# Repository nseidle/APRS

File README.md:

APRS Entry for 2016 SparkFun AVC
===========================================================

This repo contains all the code and PCB layouts used on the A+PRS vehicle Alicia and I entered in the 2016 SparkFun AVC.

Repository Contents
-------------------

The vehicle is broken into sub-systems in order to eat the elephant. Each directory is a sub-system.

Documentation
--------------

There's a tutorial being written.

License Information
-------------------

This is _**open source**_! 

Please use, reuse, and modify these files as you see fit. Please maintain attribution to SparkFun Electronics. Any derivative must be released under the same license.

Distributed as-is; no warranty is given.

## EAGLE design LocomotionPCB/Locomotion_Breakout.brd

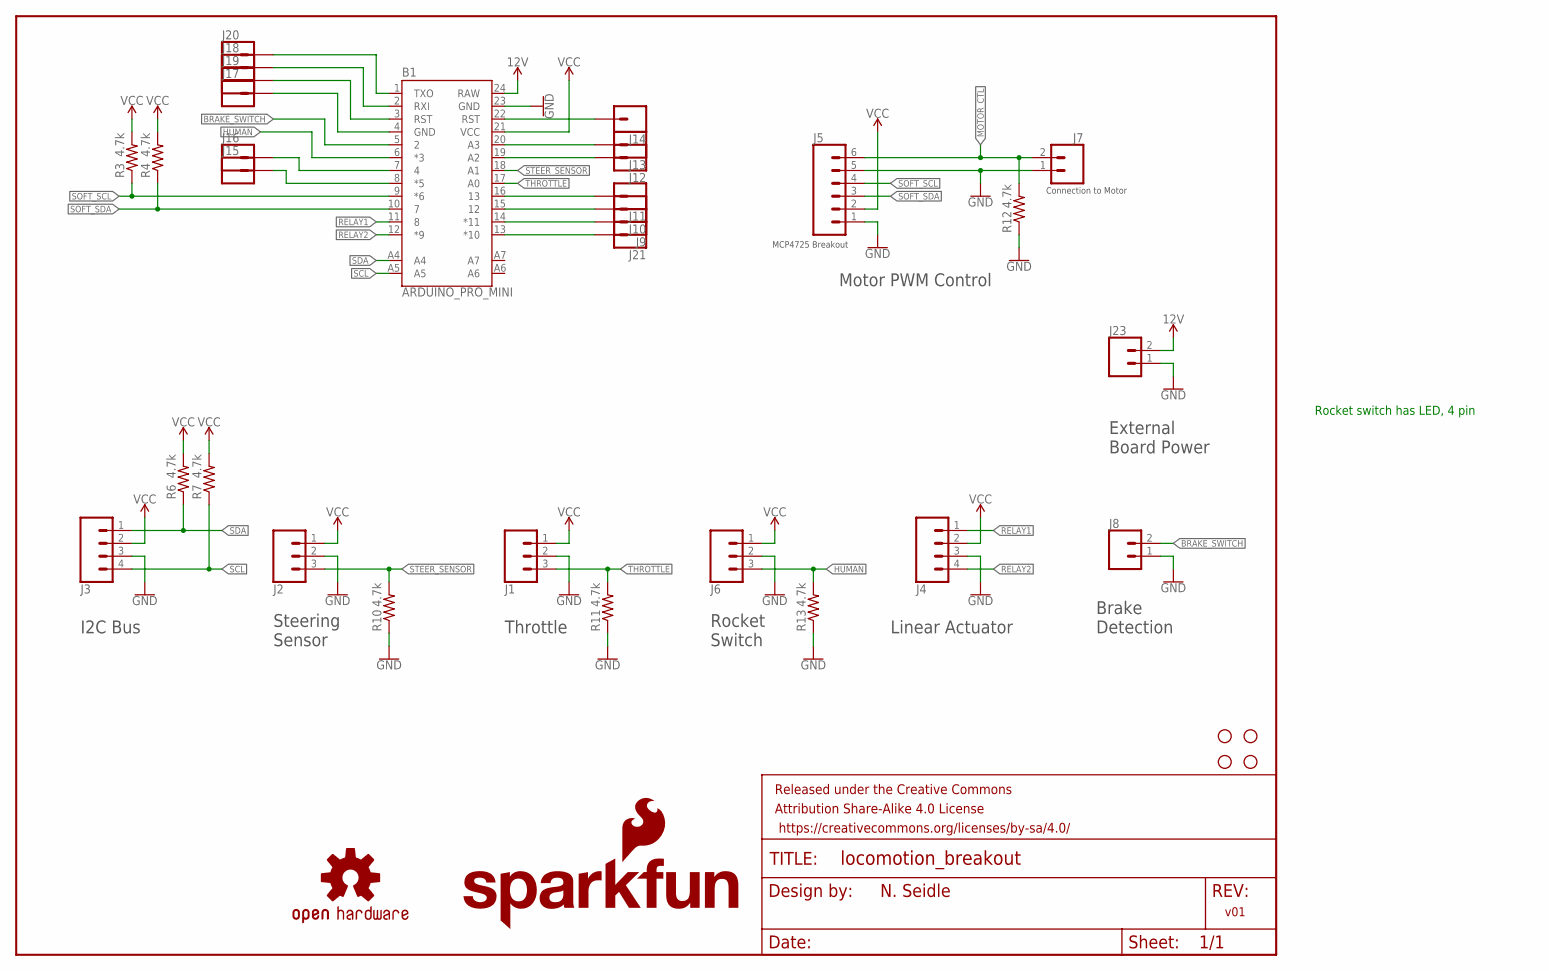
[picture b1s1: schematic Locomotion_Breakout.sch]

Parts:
B1: ARDUINO_PRO_MINI
FRAME1: FRAME-LETTER; CREATIVE_COMMONS
J1, J2, J6: CONN_03JST-PTH-VERT; JST-3-PTH-VERT
J3, J4: CONN_04JST-PTH-VERT; JST-4-PTH-VERT
J5: CONN_06SILK_FEMALE_PTH; 1X06
J7, J8, J23: CONN_02JST-PTH-VERT; JST-2-PTH-VERT
J9, J10, J11, J12, J13, J14, J15, J16, J17, J18, J19, J20, J21: CONN_01PTH_NO_SILK_YES_STOP; 1X01_NO_SILK
LOGO1: SFE_LOGO_FLAME.1_INCH; SFE_LOGO_FLAME_.1
LOGO2: OSHW-LOGOS; OSHW-LOGO-S
LOGO3: SFE_LOGO_NAME.1_INCH; SFE_LOGO_NAME_.1
R3, R4, R6, R7, R10, R11, R12, R13: 4.7k; AXIAL-0.3
STANDOFF1, STANDOFF2, STANDOFF3, STANDOFF4: STAND-OFF

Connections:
12V: B1.24 (RAW), J23.2
BRAKE_SWITCH: B1.5 (2), J8.2
GND: B1.23 (GND), J1.2, J2.2, J3.3, J4.3, J5.1, J5.5, J6.2, J7.1, J8.1, J23.1, R10.P$1 (1), R11.P$1 (1), R12.P$1 (1), R13.P$1 (1)
HUMAN: B1.6 (*3), J6.3, R13.P$2 (2)
MOTOR_CTL: J5.6, J7.2, R12.P$2 (2)
unnamed: B1.2 (RXI), J18.1
unnamed: B1.3 (RST), J19.1
unnamed: B1.4 (GND), J17.1
unnamed: B1.7 (4), J16.1
unnamed: B1.8 (*5), J15.1
unnamed: B1.13 (*10), J21.1
unnamed: B1.14 (*11), J9.1
unnamed: B1.15 (12), J10.1
unnamed: B1.16 (13), J11.1
unnamed: B1.19 (A2), J12.1
unnamed: B1.20 (A3), J13.1
unnamed: B1.22 (RST), J14.1
unnamed: B1.1 (TXO), J20.1
RELAY1: B1.11 (8), J4.1
RELAY2: B1.12 (*9), J4.4
SCL: B1.A5, J3.4, R7.P$1 (1)
SDA: B1.A4, J3.1, R6.P$1 (1)
SOFT_SCL: B1.9 (*6), J5.4, R3.P$1 (1)
SOFT_SDA: B1.10 (7), J5.3, R4.P$1 (1)
STEER_SENSOR: B1.18 (A1), J2.3, R10.P$2 (2)
THROTTLE: B1.17 (A0), J1.3, R11.P$2 (2)
VCC: B1.21 (VCC), J1.1, J2.1, J3.2, J4.2, J5.2, J6.1, R3.P$2 (2), R4.P$2 (2), R6.P$2 (2), R7.P$2 (2)

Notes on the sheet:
v01
N. Seidle
Throttle
I2C Bus
Linear Actuator
Motor PWM Control
MCP4725 Breakout
Connection to Motor
Steering Sensor
Rocket Switch
Brake Detection
External Board Power
Rocket switch has LED, 4 pin

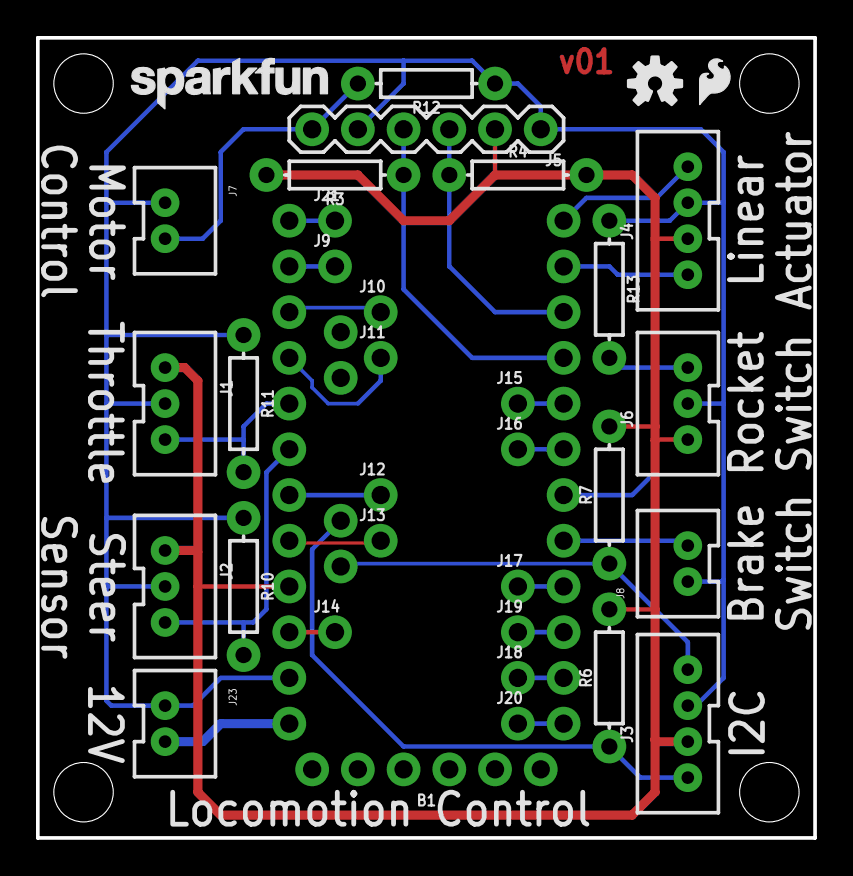
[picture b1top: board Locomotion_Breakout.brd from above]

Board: 2 copper layers, 43.2 x 44.5 mm, 39 parts (0 on the bottom side), 27 nets.

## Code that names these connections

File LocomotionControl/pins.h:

//Hardware definitions
//-=-=-=-=-=-=-=-=-=-=-=-=-=-=-=-=-=-=-=-=-=-=-=-=-=-=-=-=-=-=-=-=-=-=-=-=-=-=-=-=-=-=
#define THROTTLE_IN A0

//#define THROTTLE_OUT 9 //PWM base frequency is 31250 Hz, above hearing range

#define STEER_POT A1

//The rocket switch is wired super weird. The pin on side is LED common. And LED gets power from either
//of the lower lugs (+). Lug on left is wired 5V, lug on right is wired switch with a pull-down.
//So when rocket is thrown, 5V goes to switch and also to LED. When LED goes low, LED turns on.
#define MODE_SWITCH_LED 4 //Yellow
#define MODE_SWITCH 3 //Black

#define RELAY1 8
#define RELAY2 9

#define BRAKE_SWITCH 2

#define STAT 13
//-=-=-=-=-=-=-=-=-=-=-=-=-=-=-=-=-=-=-=-=-=-=-=-=-=-=-=-=-=-=-=-=-=-=-=-=-=-=-=-=-=-=

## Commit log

2016-10-23 :octocat: Added .gitattributes & .gitignore files
2016-10-23 Initial rough commit
2016-10-23 Adding image to readme

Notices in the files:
parts and their libraries:
SparkFun-Aesthetics: Licensing: CC v3.0 Share-Alike You are welcome to use this library for commercial purposes.
SparkFun-Aesthetics: Released under the Creative Commons Attribution Share-Alike 4.0 License
SparkFun-Aesthetics: https://creativecommons.org/licenses/by-sa/4.0
